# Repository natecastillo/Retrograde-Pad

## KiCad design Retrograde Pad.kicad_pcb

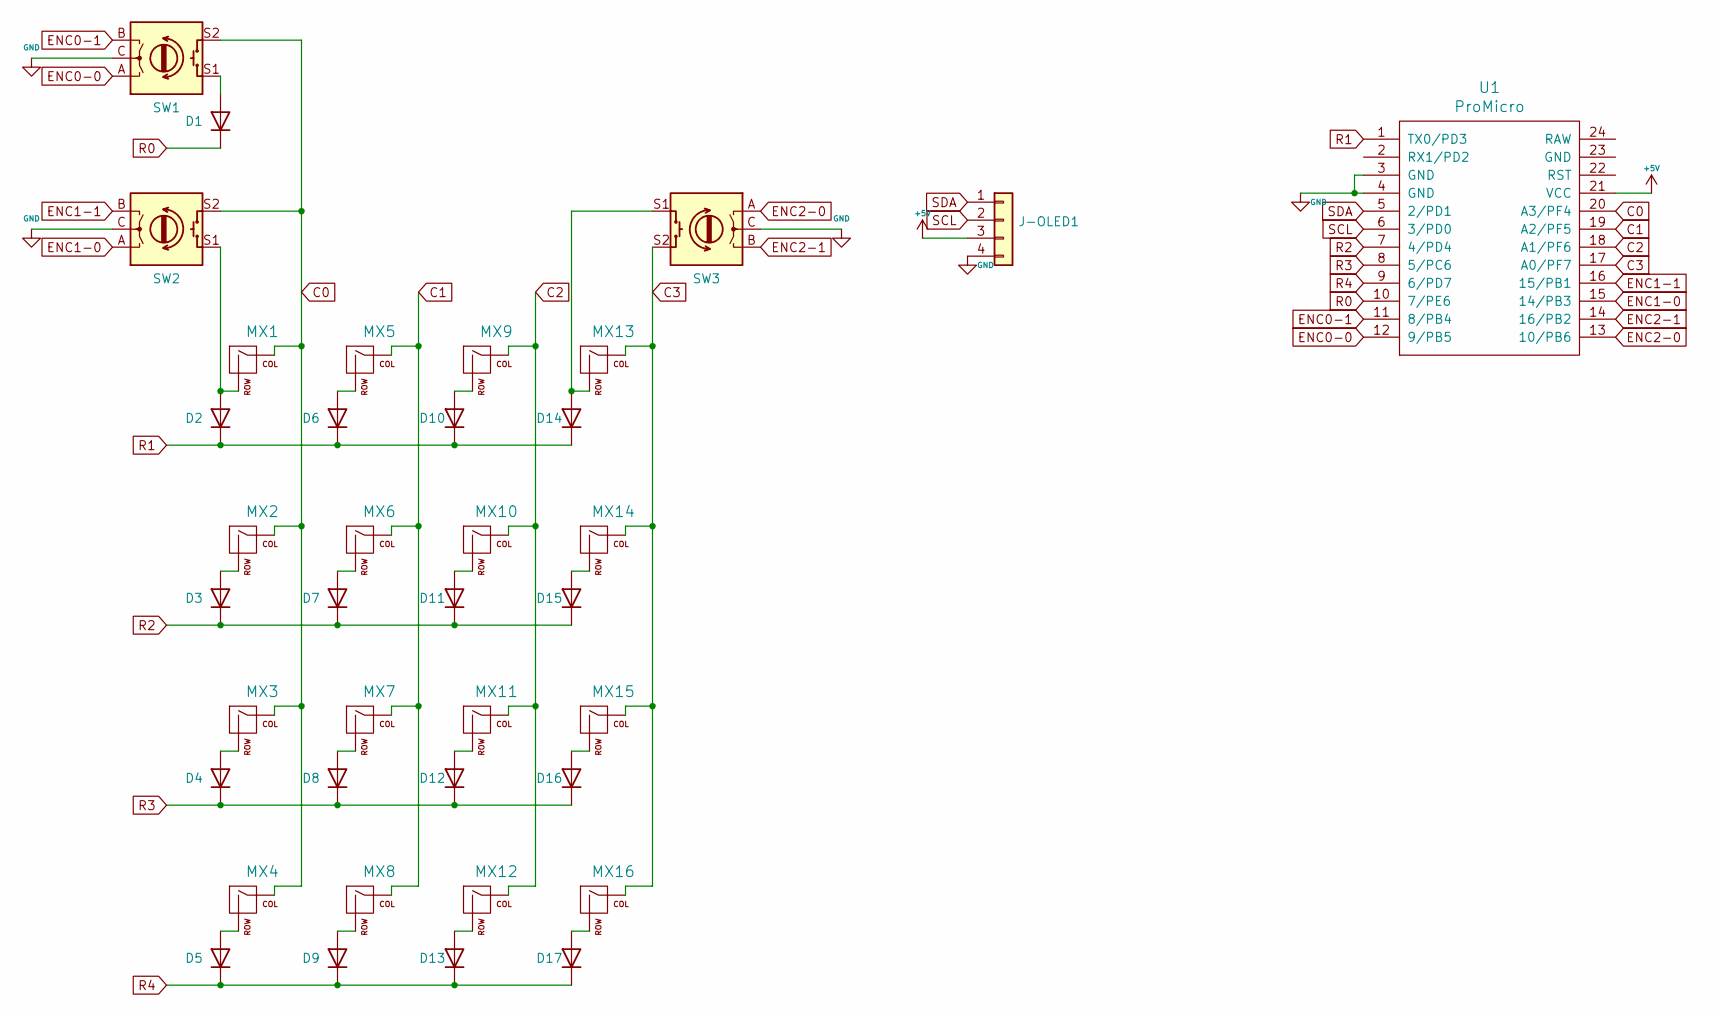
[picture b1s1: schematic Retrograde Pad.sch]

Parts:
D1, D2, D3, D4, D5, D6, D7, D8, D9, D10, D11, D12, D13, D14, D15, D16, D17: 1N4148; D_DO-35_SOD27_P7.62mm_Horizontal
J-OLED1: Conn_01x04; PinHeader_1x04_P2.54mm_Vertical
MX1, MX2, MX3, MX4, MX5, MX6, MX7, MX8, MX9, MX10, MX11, MX12, MX13, MX14, MX15, MX16: MX-LED; MXOnly-1U-NoLED
SW1, SW2, SW3: Rotary_Encoder_Switch; RotaryEncoder_Alps_EC11E-Switch_Vertical_H20mm
U1: ProMicro; ArduinoProMicro

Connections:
+5V: J-OLED1.3, U1.21 (VCC)
C0: MX1.1 (COL), MX2.1 (COL), MX3.1 (COL), MX4.1 (COL), SW1.S2, SW2.S2, U1.20 (A3/PF4)
C1: MX5.1 (COL), MX6.1 (COL), MX7.1 (COL), MX8.1 (COL), U1.19 (A2/PF5)
C2: MX9.1 (COL), MX10.1 (COL), MX11.1 (COL), MX12.1 (COL), U1.18 (A1/PF6)
C3: MX13.1 (COL), MX14.1 (COL), MX15.1 (COL), MX16.1 (COL), SW3.S2, U1.17 (A0/PF7)
ENC0-0: SW1.A, U1.12 (9/PB5)
ENC0-1: SW1.B, U1.11 (8/PB4)
ENC1-0: SW2.A, U1.15 (14/PB3)
ENC1-1: SW2.B, U1.16 (15/PB1)
ENC2-0: SW3.A, U1.13 (10/PB6)
ENC2-1: SW3.B, U1.14 (16/PB2)
GND: J-OLED1.4, SW1.C, SW2.C, SW3.C, U1.3 (GND), U1.4 (GND)
unnamed: D1.2 (A), SW1.S1
unnamed: D2.2 (A), MX1.2 (ROW), SW2.S1
unnamed: D3.2 (A), MX2.2 (ROW)
unnamed: D4.2 (A), MX3.2 (ROW)
unnamed: D5.2 (A), MX4.2 (ROW)
unnamed: D6.2 (A), MX5.2 (ROW)
unnamed: D7.2 (A), MX6.2 (ROW)
unnamed: D8.2 (A), MX7.2 (ROW)
unnamed: D9.2 (A), MX8.2 (ROW)
unnamed: D10.2 (A), MX9.2 (ROW)
unnamed: D11.2 (A), MX10.2 (ROW)
unnamed: D12.2 (A), MX11.2 (ROW)
unnamed: D13.2 (A), MX12.2 (ROW)
unnamed: D14.2 (A), MX13.2 (ROW), SW3.S1
unnamed: D15.2 (A), MX14.2 (ROW)
unnamed: D16.2 (A), MX15.2 (ROW)
unnamed: D17.2 (A), MX16.2 (ROW)
R0: D1.1 (K), U1.10 (7/PE6)
R1: D2.1 (K), D6.1 (K), D10.1 (K), D14.1 (K), U1.1 (TX0/PD3)
R2: D3.1 (K), D7.1 (K), D11.1 (K), D15.1 (K), U1.7 (4/PD4)
R3: D4.1 (K), D8.1 (K), D12.1 (K), D16.1 (K), U1.8 (5/PC6)
R4: D5.1 (K), D9.1 (K), D13.1 (K), D17.1 (K), U1.9 (6/PD7)
SCL: J-OLED1.2, U1.6 (3/PD0)
SDA: J-OLED1.1, U1.5 (2/PD1)

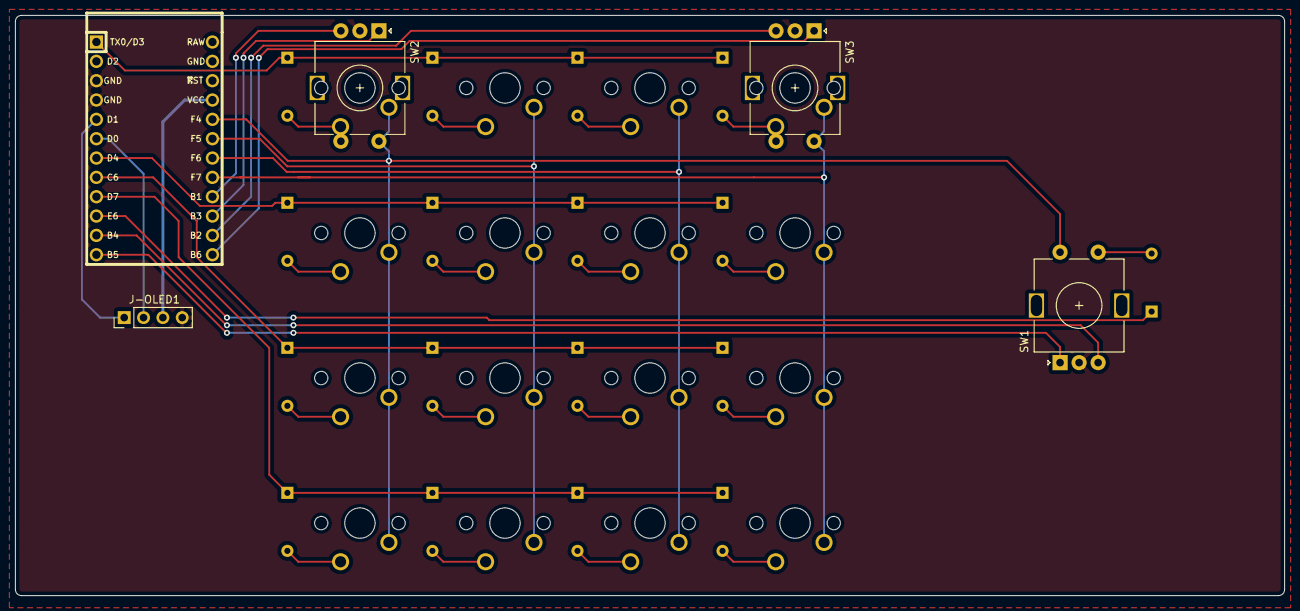
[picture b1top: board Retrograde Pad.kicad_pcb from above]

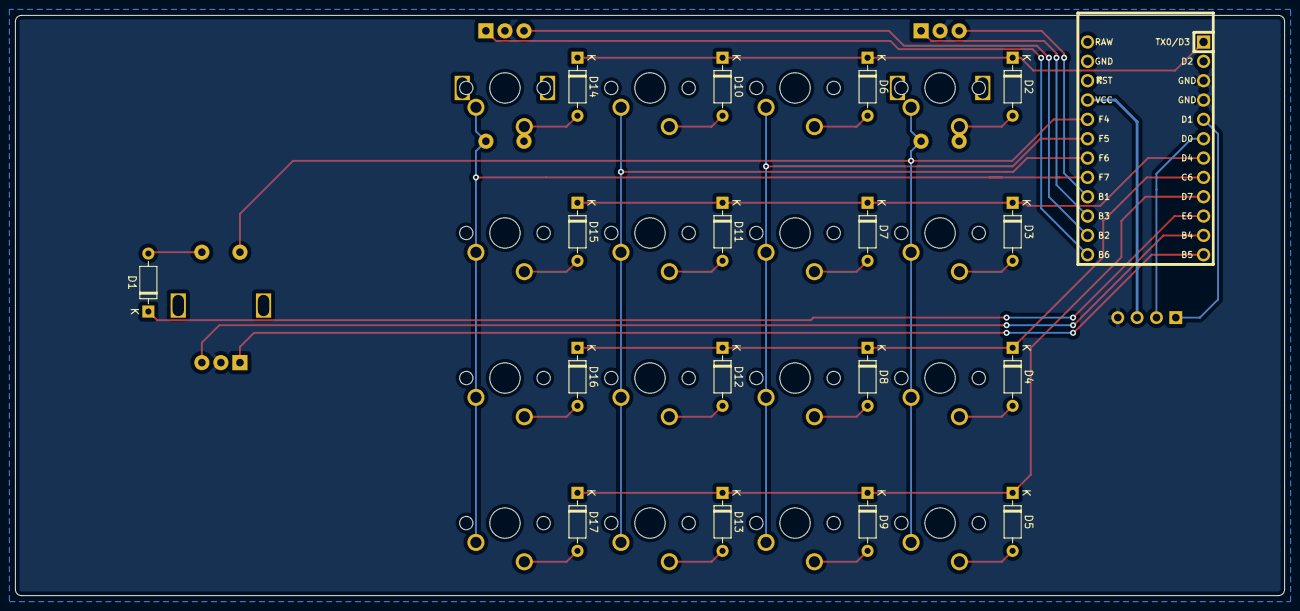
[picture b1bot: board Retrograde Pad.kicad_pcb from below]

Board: 2 copper layers, 166.7 x 76.2 mm, 38 parts (17 on the bottom side), 36 nets.

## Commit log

2021-04-18 Upload files
